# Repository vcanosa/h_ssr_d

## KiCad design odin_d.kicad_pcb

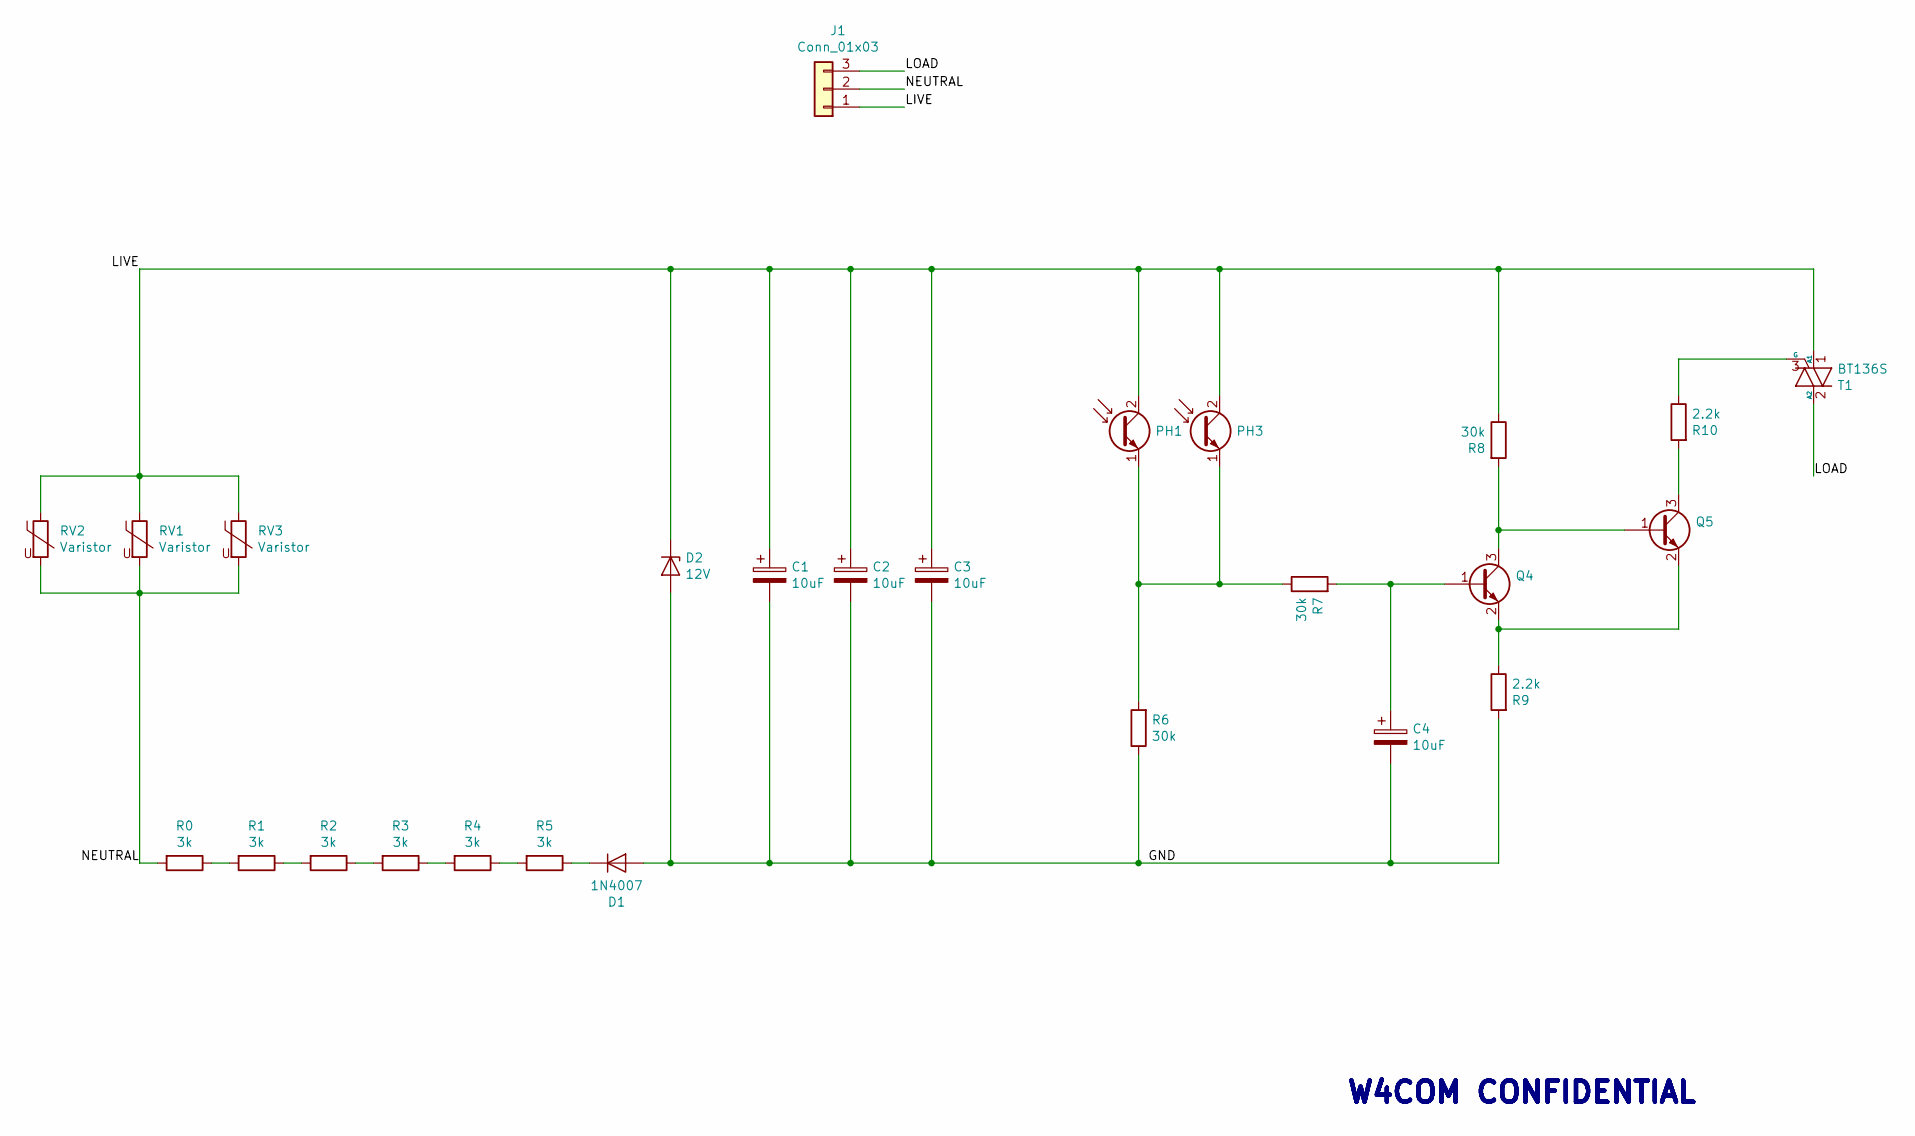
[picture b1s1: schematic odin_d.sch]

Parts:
C1, C2, C3, C4: 10uF; C_0805_2012Metric; MPN 10uF 25V
D1: 1N4007; D_SOD-123; MPN C260857
D2: 12V; D_SOD-123; MPN ZMM55-C12_R1_10001
J1: Conn_01x03; nema_3_pin_chinese; MPN MECÂNICA
PH1: Q_Photo_NPN_EC; R_0805_2012Metric
PH3: Q_Photo_NPN_EC; R_1206_3216Metric
Q4, Q5: Q_NPN_BEC; SOT-23; MPN PMBT3904,215
R0, R1, R2, R3, R4, R5: 3k; R_1210_3225Metric; MPN 0805W8J0473T5E
R6, R7, R8: 30k; R_0805_2012Metric
R9, R10: 2.2k; R_0805_2012Metric; MPN RS-03K1001FT
RV1: Varistor; RV_Disc_D12mm_W4.3mm_P7.5mm; MPN S20K320
RV2: Varistor; RV_Disc_D9mm_W4.1mm_P5mm; MPN S20K320
RV3: Varistor; RV_Disc_D21.5mm_W5.8mm_P10mm; MPN S20K320
T1: BT136S; TO-252-2; MPN BT136S

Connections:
/GND: C1.2, C2.2, C3.2, C4.2, D1.2 (A), D2.2 (A), R6.1, R9.2
/LIVE: C1.1, C2.1, C3.1, D2.1 (K), J1.1, PH1.2 (C), PH3.2 (C), R8.1, RV1.1, RV2.1, RV3.1, T1.1 (A1)
/LOAD: J1.3, T1.2 (A2)
/NEUTRAL: J1.2, R0.2, RV1.2, RV2.2, RV3.2
unnamed: C4.1, Q4.1 (B), R7.2
unnamed: D1.1 (K), R5.1
unnamed: PH1.1 (E), PH3.1 (E), R6.2, R7.1
unnamed: Q4.2 (E), Q5.2 (E), R9.1
unnamed: Q4.3 (C), Q5.1 (B), R8.2
unnamed: Q5.3 (C), R10.2
unnamed: R0.1, R1.2
unnamed: R1.1, R2.2
unnamed: R2.1, R3.2
unnamed: R3.1, R4.2
unnamed: R4.1, R5.2
unnamed: R10.1, T1.3 (G)

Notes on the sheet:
W4COM CONFIDENTIAL

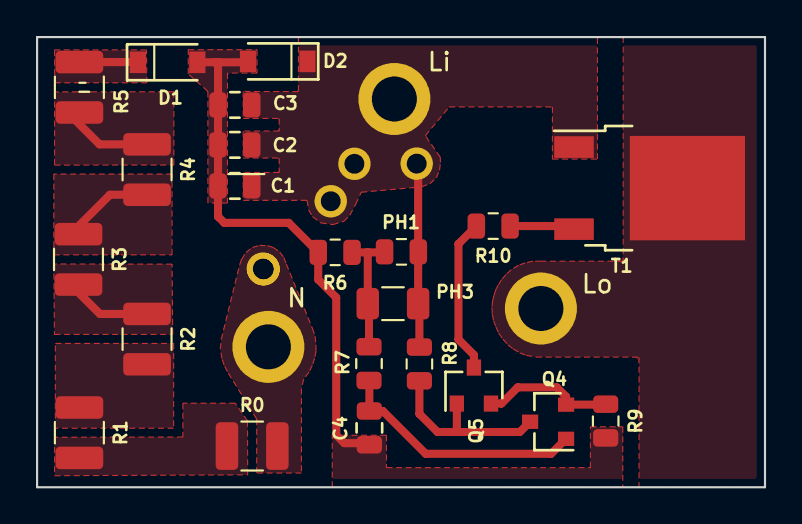
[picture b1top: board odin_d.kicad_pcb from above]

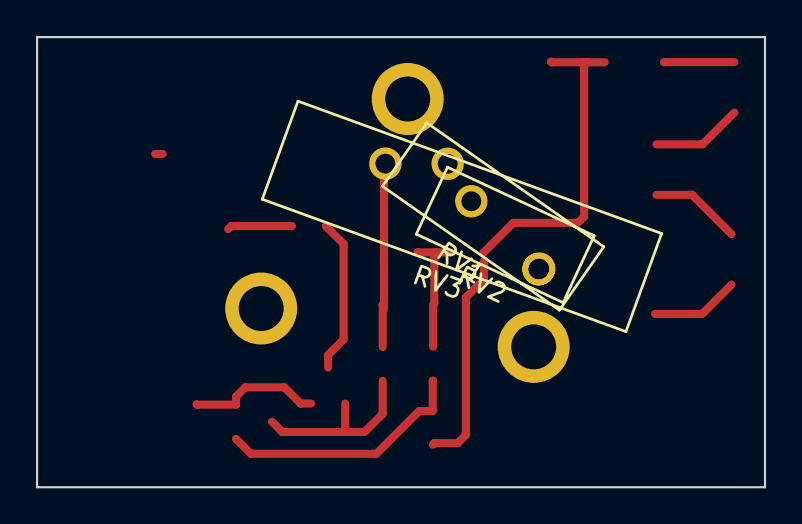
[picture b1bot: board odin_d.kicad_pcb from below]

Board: 2 copper layers, 40.4 x 25.0 mm, 26 parts (3 on the bottom side), 16 nets.

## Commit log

2021-03-29 Repository for 220/110 vac solid state relay version
2021-03-29 Added 1210 footprint resistor for 110/220 VAC version
2021-03-30 Version compatible with fuse relay so the same stencial can be used for both
2021-05-06 Added files for production run
2021-05-07 Silk screen layer corrected and drill files al included
